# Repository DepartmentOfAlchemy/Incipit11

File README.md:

# Incipit11
Low power light dimmer

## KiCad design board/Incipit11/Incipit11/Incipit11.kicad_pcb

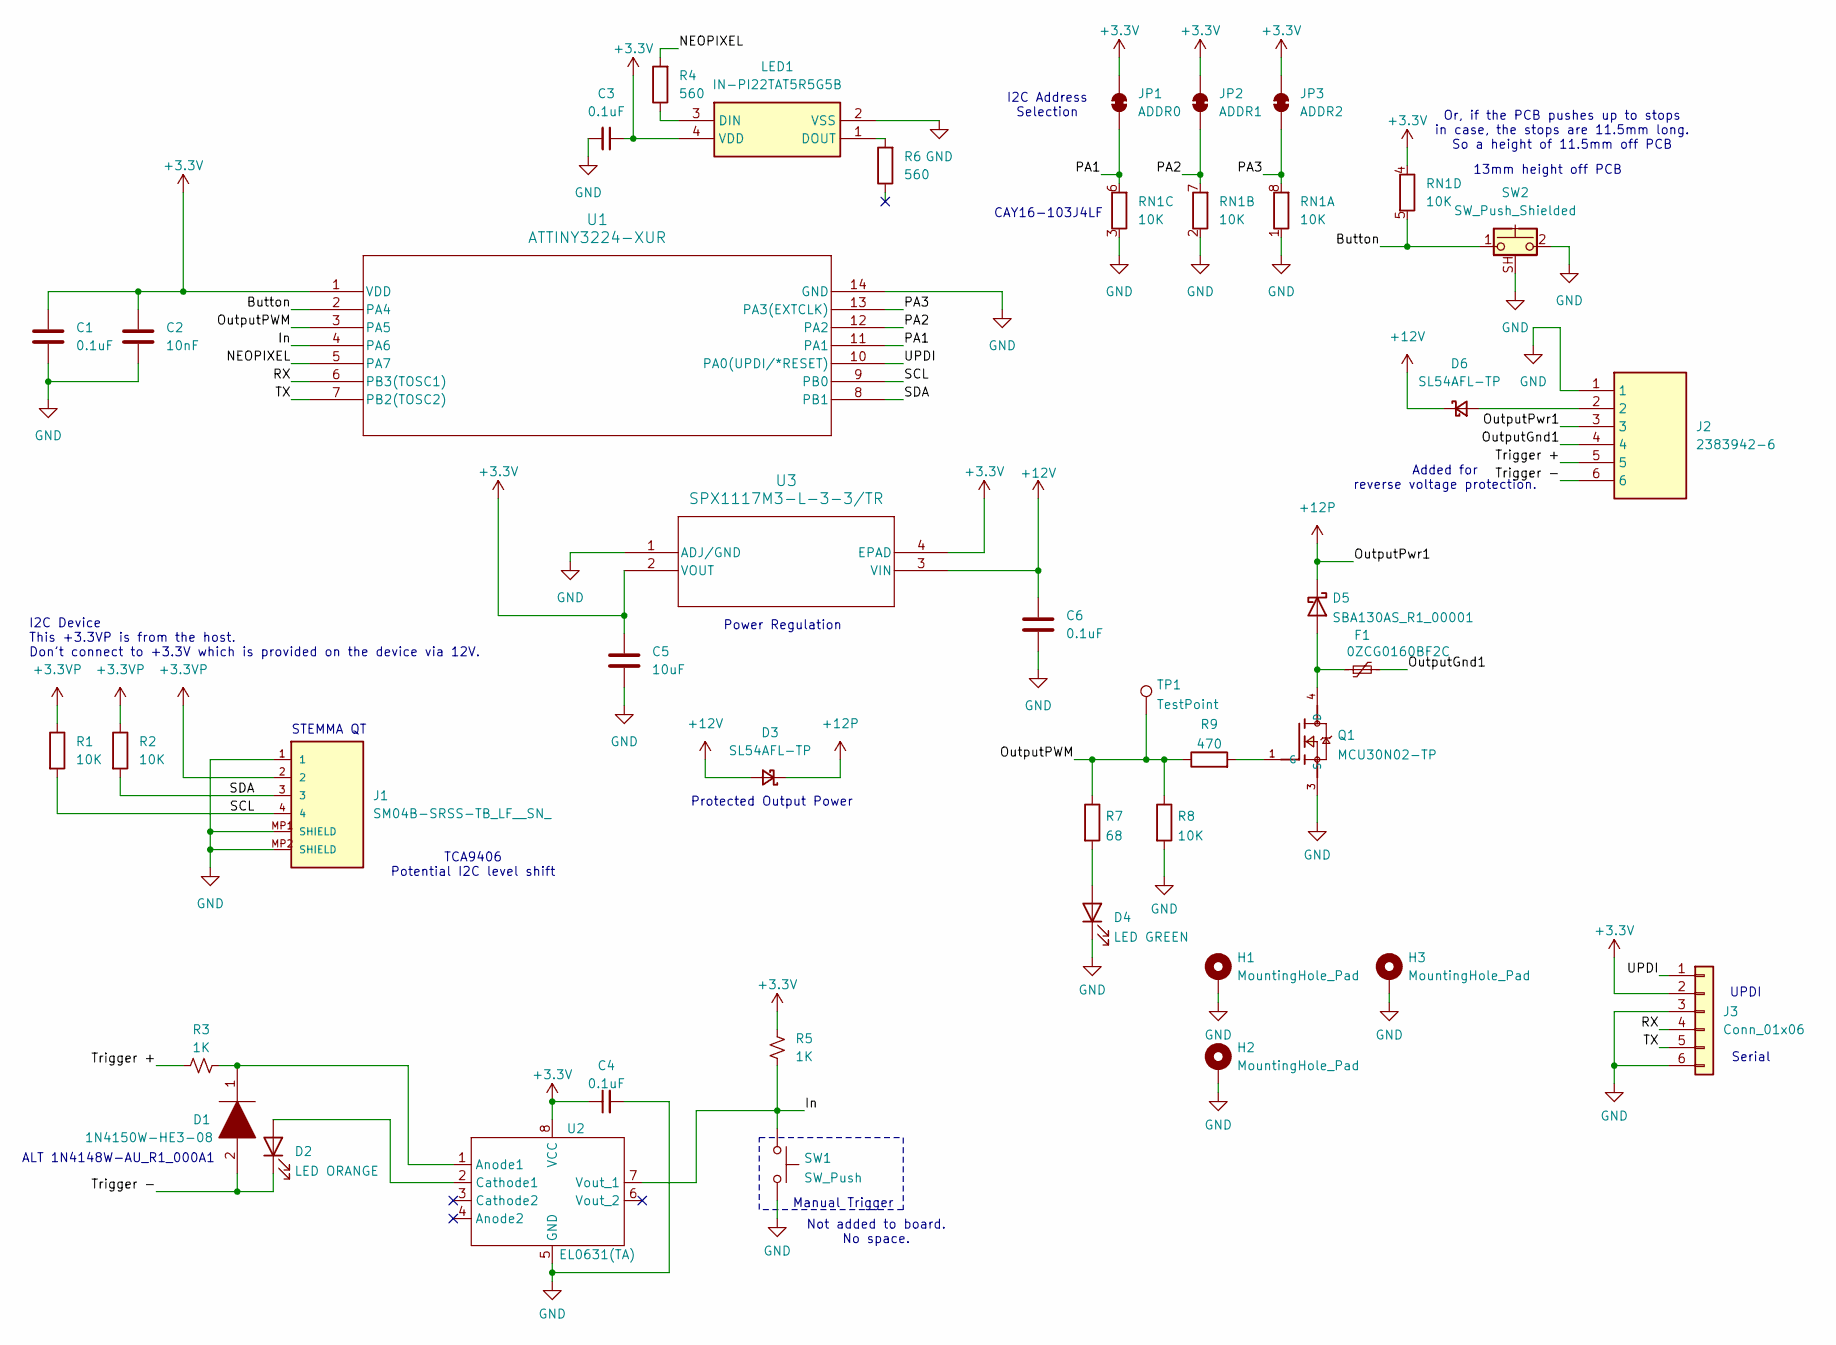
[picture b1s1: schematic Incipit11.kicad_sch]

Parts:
C1, C3, C4, C6: 0.1uF; C_0603_1608Metric
C2: 10nF; C_0603_1608Metric
C5: 10uF; C_0805_2012Metric
D1: 1N4150W-HE3-08; D_SOD-123; Manufacturer_Part_Number S1GTR
D2: LED ORANGE; LED_0603_1608Metric
D3, D6: SL54AFL-TP; SL54AFL-TP DO-221AC(SMA-FL)
D4: LED GREEN; LED_0603_1608Metric
D5: SBA130AS_R1_00001; D_SOD-123
F1: 0ZCG0160BF2C; Fuse_1812_4532Metric
H1, H2, H3: MountingHole_Pad; MountingHole_2.2mm_M2_ISO7380_Pad_TopBottom
J1: SM04B-SRSS-TB_LF__SN_; JST_SH_BM04B-SRSS-TB_1x04-1MP_P1.00mm_Vertical
J2: 2383942-6; 393570006; Manufacturer_Part_Number 2383942-6; Mouser Part Number 571-2383942-6
J3: Conn_01x06; PinHeader_1x06_P2.54mm_Vertical
JP1: ADDR0; SolderJumper-2_P1.3mm_Bridged_RoundedPad1.0x1.5mm
JP2: ADDR1; SolderJumper-2_P1.3mm_Bridged_RoundedPad1.0x1.5mm
JP3: ADDR2; SolderJumper-2_P1.3mm_Bridged_RoundedPad1.0x1.5mm
LED1: IN-PI22TAT5R5G5B; INPI22TAT5R5G5B; Mouser Part Number 743-IN-PI22TAT5R5G5B
Q1: MCU30N02-TP; TO229P991X239-3N
R1, R2, R8: 10K; R_0603_1608Metric
R3, R5: 1K; R_0603_1608Metric
R4, R6: 560; R_0603_1608Metric
R7: 68; R_0603_1608Metric
R9: 470; R_0603_1608Metric
RN1: 10K; R_Array_Convex_4x0603
SW1: SW_Push; SW_Push_1P1T_NO_RKB2SJK250SMTR LFS
SW2: SW_Push_Shielded; CT1102P
TP1: TestPoint; TestPoint_Pad_D2.5mm
U1: ATTINY3224-XUR; TSSOP14_ST_MCH
U2: EL0631(TA); EL0631(TA)-SOP-8_3.9x4.9mm_P1.27mm
U3: SPX1117M3-L-3-3/TR; SOT223-3_MXL

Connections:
+3.3V: C1.2, C2.2, C3.1, C4.1, C5.1, J3.2, JP1.2 (B), JP2.2 (B), JP3.2 (B), LED1.4 (VDD), R5.2, RN1.4 (R4.1), U1.1 (VDD), U2.8 (VCC), U3.2 (VOUT), U3.4 (EPAD)
+3.3VP: J1.2, R1.1, R2.1
+12P: D3.1 (K), D5.1 (K), J2.3
+12V: C6.1, D3.2 (A), D6.1 (K), U3.3 (VIN)
/Button: RN1.5 (R4.2), SW2.1, U1.2 (PA4)
/In: R5.1, SW1.1, U1.4 (PA6), U2.7 (Vout_1)
/NEOPIXEL: R4.2, U1.5 (PA7)
/OutputGnd1: F1.2, J2.4
/OutputPWM: R7.1, R8.1, R9.1, TP1.1, U1.3 (PA5)
/PA1: JP1.1 (A), RN1.6 (R3.2), U1.11 (PA1)
/PA2: JP2.1 (A), RN1.7 (R2.2), U1.12 (PA2)
/PA3: JP3.1 (A), RN1.8 (R1.2), U1.13 (PA3(EXTCLK))
/RX: J3.4, U1.6 (PB3(TOSC1))
/SCL: J1.4, R1.2, U1.9 (PB0)
/SDA: J1.3, R2.2, U1.8 (PB1)
/TX: J3.5, U1.7 (PB2(TOSC2))
/Trigger +: J2.5, R3.2
/Trigger -: D1.2, D2.1 (K), J2.6
/UPDI: J3.1, U1.10 (PA0(UPDI/*RESET))
GND: C1.1, C2.1, C3.2, C4.2, C5.2, C6.2, D4.1 (K), H1.1, H2.1, H3.1, J1.1, J1.MP1 (SHIELD), J1.MP2 (SHIELD), J2.1, J3.3, J3.6, LED1.2 (VSS), Q1.3 (S), R8.2, RN1.1 (R1.1), RN1.2 (R2.1), RN1.3 (R3.1), SW1.2, SW2.2, SW2.SH (B), U1.14 (GND), U2.5 (GND), U3.1 (ADJ/GND)
unnamed: D2.2 (A), U2.2 (Cathode1)
unnamed: D4.2 (A), R7.2
unnamed: D5.2 (A), F1.1, Q1.4 (D)
unnamed: D6.2 (A), J2.2
unnamed: LED1.3 (DIN), R4.1
unnamed: LED1.1 (DOUT), R6.2
unnamed: Q1.1 (G), R9.2
unnamed: D1.1, R3.1, U2.1 (Anode1)

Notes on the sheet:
UPDI
Or, if the PCB pushes up to stops in case, the stops are 11.5mm long. So a height of 11.5mm off PCB
ALT 1N4148W-AU_R1_000A1
Manual Trigger
STEMMA QT
TCA9406 Potential I2C level shift
Power Regulation
13mm height off PCB
Added for reverse voltage protection.
Protected Output Power
Serial
I2C Device This +3.3VP is from the host. Don't connect to +3.3V which is provided on the device via 12V.
CAY16-103J4LF
Not added to board. No space.
I2C Address Selection

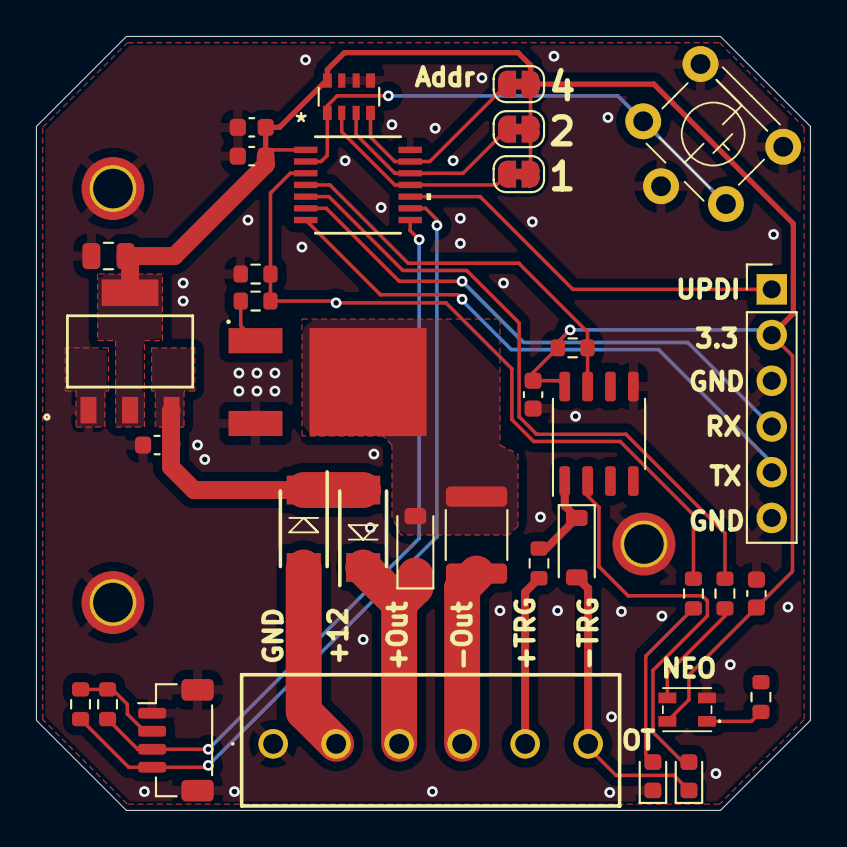
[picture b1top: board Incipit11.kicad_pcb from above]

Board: 2 copper layers, 43.0 x 43.0 mm, 39 parts (1 on the bottom side), 28 nets.

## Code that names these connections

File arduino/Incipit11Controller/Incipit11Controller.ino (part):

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volatile uint32_t g_bufferedBulkGPIORead = 0;

//#define CONFIG_ADDR_INVERTED
#define CONFIG_ADDR_0_PIN PIN_PA1
#define CONFIG_ADDR_1_PIN PIN_PA2
#define CONFIG_ADDR_2_PIN PIN_PA3

#include "DOA_seesawCompatibility.h"
// end Adafruit Seesaw compatibility
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#include <EEPROM.h>
#include <Wire.h>

#define PWM_OUTPUT PIN_PA5
#define NEOPIXEL   PIN_PA7
#define TX         PIN_PB2
#define RX         PIN_PB3

#define PIN_BUTTON  PIN_PA4
#define PIN_TRIGGER PIN_PA6

const uint32_t MILLIS_30_MINUTES = 1800000L;
const uint32_t MILLIS_10_SECONDS = 10000L;
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  // put your setup code here, to run once:
  // put your setup code here, to run once:
  pinMode(PWM_OUTPUT, OUTPUT);
  pinModeFast(NEOPIXEL, OUTPUT);

  // Seesaw setup
  DOA_seesawCompatibility_setPWMCallback(&PWMCallback);
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
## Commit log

2025-04-12 Rev A of the project.
2025-05-14 Rev B of board for new case. Did a few modifications to add more reverse protection on output and changed the I2C to seperate the 3.3 power from controller and peripheral.
2026-02-01 Updates to support using the Incipit 11 (Rev C) as an Adafruit Seesaw peripheral. Basic functionality works. The SeesawTest Arduino program was used to test the basic functionality.
2026-02-03 Renamed Flicker effect to FlickerOff and added a FlickerOn effect. Refactored setting Seesaw communicated PWM and reset to registered callback functions instead of global variables. Refectored cyclin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
2026-02-05 Added Sine Wave and Heartbeat effects. Added Seesaw peripheral support to read/write the ambient effect, triggered effect, and triggered effect length. Also added Seesaw peripheral support for activi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
